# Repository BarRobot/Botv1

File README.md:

# Botv1
BarRobot is a South African design for a Bartending Robot machine.  
It comes with a really easy to use user interface: Selector Switch to choose Single, Double.  And one big red illuminited "Go" button.  Can't be easier!
WS2812B LEDs surround the spirits bottle, helping to invite friends closer - attracted by RGB Blinkies!

## Electronics:
This is a render of the Version 1 Electronics Pack 

## Mascot! 

This is our official Mascot, designed by the talented [LUISDJT](https://www.fiverr.com/luisdjt) - Thanks for the cool Mascot!

## Early prototypes in action

Here's an old version, in use:

(Youtube Link)

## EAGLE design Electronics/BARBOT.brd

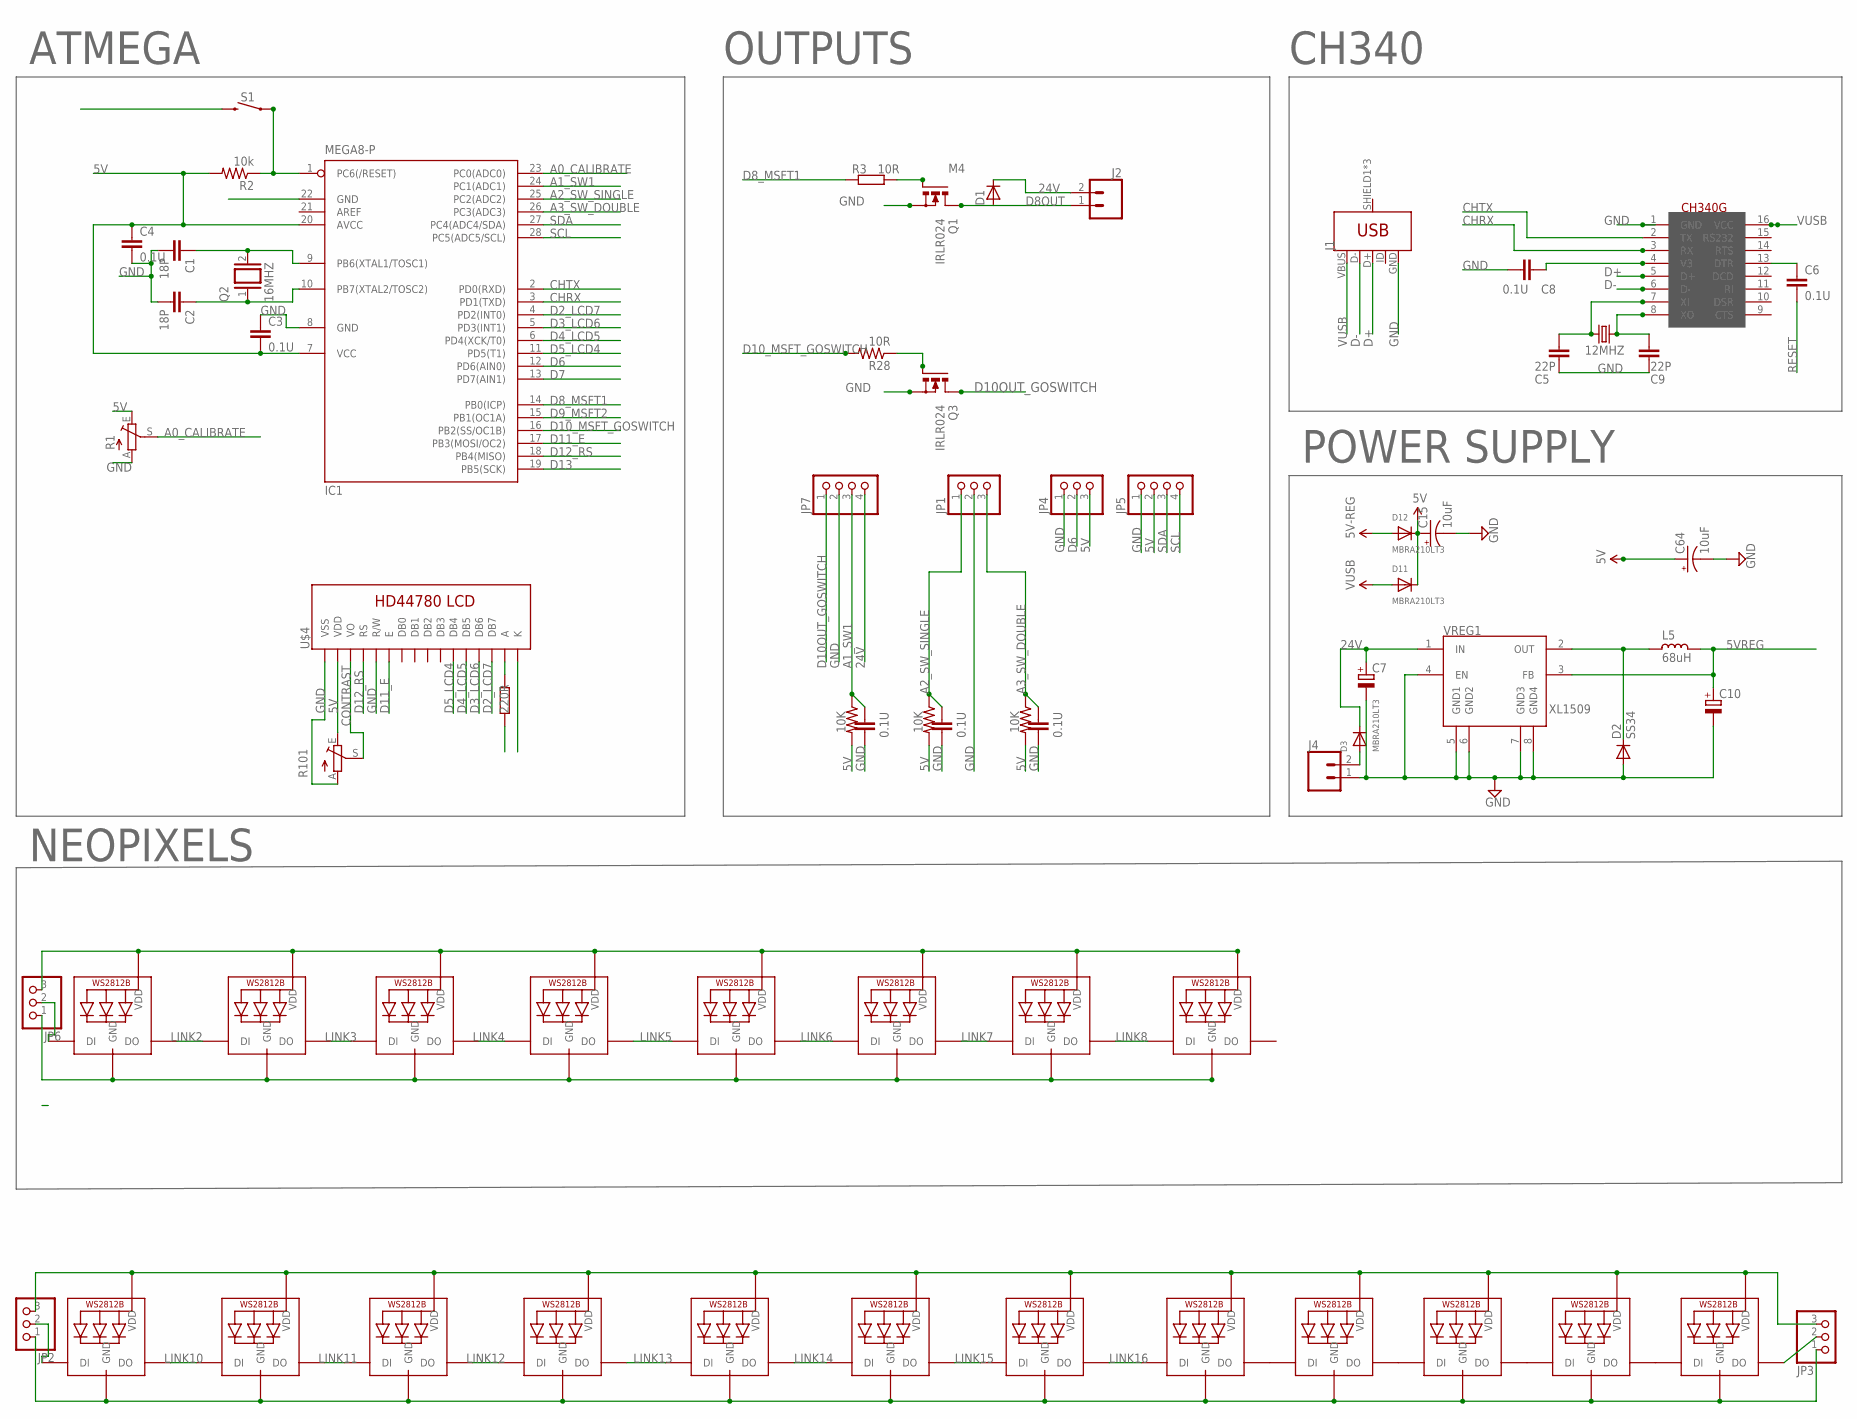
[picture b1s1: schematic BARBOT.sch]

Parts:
12MHZ: 12MHZ; HC49U70
C1, C2: 18P; C1206
C3, C4, C6, C8, C11, C12, C13: 0.1U; C1206
C5, C9: 22P; C1206
C7, C10: CPOL-EUE3.5-10; E3,5-10
C15, C64: 10uF; EIA3216
D1: M4; SOD80
D2: SS34; DO-214AC
D3, D11, D12: MBRA210LT3; SMADIODE
IC1: MEGA8-P; DIL28-3
J1: USB_MICRO-BREDUCED_PASTE; USB-B-MICRO-SMD_RED_PASTE
J2, J4: CONN_023.5MM; SCREWTERMINAL-3.5MM-2
JP1, JP2, JP3, JP4, JP6: PINHD-1X3; 1X03
JP5, JP7: PINHD-1X4; 1X04
L5: 68uH; CD75
LED1, LED2, LED3, LED4, LED5, LED6, LED7, LED8, LED9, LED10, LED11, LED12, LED13, LED14, LED15, LED16, LED17, LED18, LED19, LED20: WS2812B5050; WS2812B
Q1, Q3: IRLR024; D-PAK_TO252AA
Q2: 16MHZ; QS
R1, R101: TRIM_EU-B25P; B25P
R2: 10k; R1206
R3: 10R; R1206
R4: 220R; R1206
R5, R6, R7: 10K; R1206@1
R28: 10R; R1206@1
S1: MOMENTARY-SWITCH-SPST-PTH-RIGHT-ANGLE-KIT; TACTILE_SWITCH_PTH_RIGHT_ANGLE_KIT
U$2: CH340G; SOIC16
U$4: LCD-HD447804-HOLES16X2-4-HOLES; LCD-16X2-4HOLES
VREG1: XL1509; SO08

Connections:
5V: C3.2, C4.1, C15.A (+), C64.A (+), D11.C, D12.C, IC1.7 (VCC), IC1.20 (AVCC), JP4.3, JP5.2, JP6.3, LED1.1-VDD (VDD), LED2.1-VDD (VDD), LED3.1-VDD (VDD), LED4.1-VDD (VDD), LED5.1-VDD (VDD), LED6.1-VDD (VDD), LED7.1-VDD (VDD), LED8.1-VDD (VDD), R1.E, R2.2, R4.1, R5.2, R6.2, R7.2, R101.E, U$4.2 (VDD)
5V1: JP2.3, JP3.3, LED9.1-VDD (VDD), LED10.1-VDD (VDD), LED11.1-VDD (VDD), LED12.1-VDD (VDD), LED13.1-VDD (VDD), LED14.1-VDD (VDD), LED15.1-VDD (VDD), LED16.1-VDD (VDD), LED17.1-VDD (VDD), LED18.1-VDD (VDD), LED19.1-VDD (VDD), LED20.1-VDD (VDD)
5VREG: C10.+, D12.A, L5.1, VREG1.3 (FB)
24V: C7.+, D1.1 (C), D3.C, J2.2, JP7.4, VREG1.1 (IN)
A0_CALIBRATE: IC1.23 (PC0(ADC0)), R1.S
A1_SW1: C11.1, IC1.24 (PC1(ADC1)), JP7.3, R5.1
A2_SW_SINGLE: C12.1, IC1.25 (PC2(ADC2)), JP1.1, R6.1
A3_SW_DOUBLE: C13.1, IC1.26 (PC3(ADC3)), JP1.3, R7.1
CHRX: IC1.3 (PD1(TXD)), U$2.3 (RX)
CHTX: IC1.2 (PD0(RXD)), U$2.2 (TX)
CONTRAST: R101.S, U$4.3 (VO)
D2_LCD7: IC1.4 (PD2(INT0)), U$4.14 (DB7)
D3_LCD6: IC1.5 (PD3(INT1)), U$4.13 (DB6)
D4_LCD5: IC1.6 (PD4(XCK/T0)), U$4.12 (DB5)
D5_LCD4: IC1.11 (PD5(T1)), U$4.11 (DB4)
D6: IC1.12 (PD6(AIN0)), JP4.2
D7: IC1.13 (PD7(AIN1))
D8OUT: D1.2 (A), J2.1, Q1.4 (D)
D8_MSFT1: IC1.14 (PB0(ICP)), R3.1
D9_MSFT2: IC1.15 (PB1(OC1A))
D10OUT_GOSWITCH: JP7.1, Q3.4 (D)
D10_MSFT_GOSWITCH: IC1.16 (PB2(SS/OC1B)), R28.2
D11_E: IC1.17 (PB3(MOSI/OC2)), U$4.6 (E)
D12_RS: IC1.18 (PB4(MISO)), U$4.4 (RS)
D13: IC1.19 (PB5(SCK))
D+: J1.D+, U$2.5 (D+)
D-: J1.D-, U$2.6 (D-)
GND: C1.2, C2.2, C3.1, C4.2, C5.2, C7.-, C8.2, C9.2, C10.-, C11.2, C12.2, C13.2, C15.C (-), C64.C (-), D2.2 (A), IC1.8 (GND), IC1.22 (GND), J1.GND, J4.1, JP1.2, JP4.1, JP5.1, JP6.1, JP7.2, LED1.3-GND (GND), LED2.3-GND (GND), LED3.3-GND (GND), LED4.3-GND (GND), LED5.3-GND (GND), LED6.3-GND (GND), LED7.3-GND (GND), LED8.3-GND (GND), Q1.3 (S), Q3.3 (S), R1.A, R101.A, S1.2, U$2.1 (GND), U$4.1 (VSS), U$4.5 (R/W), U$4.16 (K), VREG1.4 (EN), VREG1.5 (GND1), VREG1.6 (GND2), VREG1.7 (GND3), VREG1.8 (GND4)
GND1: JP2.1, JP3.1, LED9.3-GND (GND), LED10.3-GND (GND), LED11.3-GND (GND), LED12.3-GND (GND), LED13.3-GND (GND), LED14.3-GND (GND), LED15.3-GND (GND), LED16.3-GND (GND), LED17.3-GND (GND), LED18.3-GND (GND), LED19.3-GND (GND), LED20.3-GND (GND)
LINK1: JP6.2, LED1.4-DIN (DI)
LINK2: LED1.2-DOUT (DO), LED2.4-DIN (DI)
LINK3: LED2.2-DOUT (DO), LED3.4-DIN (DI)
LINK4: LED3.2-DOUT (DO), LED4.4-DIN (DI)
LINK5: LED4.2-DOUT (DO), LED5.4-DIN (DI)
LINK6: LED5.2-DOUT (DO), LED6.4-DIN (DI)
LINK7: LED6.2-DOUT (DO), LED7.4-DIN (DI)
LINK8: LED7.2-DOUT (DO), LED8.4-DIN (DI)
LINK9: JP2.2, LED9.4-DIN (DI)
LINK10: LED9.2-DOUT (DO), LED10.4-DIN (DI)
LINK11: LED10.2-DOUT (DO), LED11.4-DIN (DI)
LINK12: LED11.2-DOUT (DO), LED12.4-DIN (DI)
LINK13: LED12.2-DOUT (DO), LED13.4-DIN (DI)
LINK14: LED13.2-DOUT (DO), LED14.4-DIN (DI)
LINK15: LED14.2-DOUT (DO), LED15.4-DIN (DI)
LINK16: LED15.2-DOUT (DO), LED16.4-DIN (DI)
unnamed: Q1.1 (G), R3.2
unnamed: C6.1, U$2.13 (DTR)
unnamed: C1.1, IC1.9 (PB6(XTAL1/TOSC1)), Q2.2
unnamed: D3.A, J4.2
unnamed: C2.1, IC1.10 (PB7(XTAL2/TOSC2)), Q2.1
unnamed: JP3.2, LED20.2-DOUT (DO)
unnamed: LED16.2-DOUT (DO), LED17.4-DIN (DI)
unnamed: LED17.2-DOUT (DO), LED18.4-DIN (DI)
unnamed: 12MHZ.1, C5.1, U$2.7 (XI)
unnamed: R4.2, U$4.15 (A)
unnamed: 12MHZ.2, C9.1, U$2.8 (XO)
unnamed: C8.1, U$2.4 (V3)
unnamed: LED18.2-DOUT (DO), LED19.4-DIN (DI)
unnamed: LED19.2-DOUT (DO), LED20.4-DIN (DI)
unnamed: Q3.1 (G), R28.1
unnamed: D2.1 (C), L5.2, VREG1.2 (OUT)
RESET: C6.2, IC1.1 (PC6(/RESET)), R2.1, S1.1
SCL: IC1.28 (PC5(ADC5/SCL)), JP5.4
SDA: IC1.27 (PC4(ADC4/SDA)), JP5.3
VUSB: D11.A, J1.VBUS, U$2.16 (VCC)

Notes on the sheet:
POWER SUPPLY
OUTPUTS
ATMEGA
CH340
NEOPIXELS

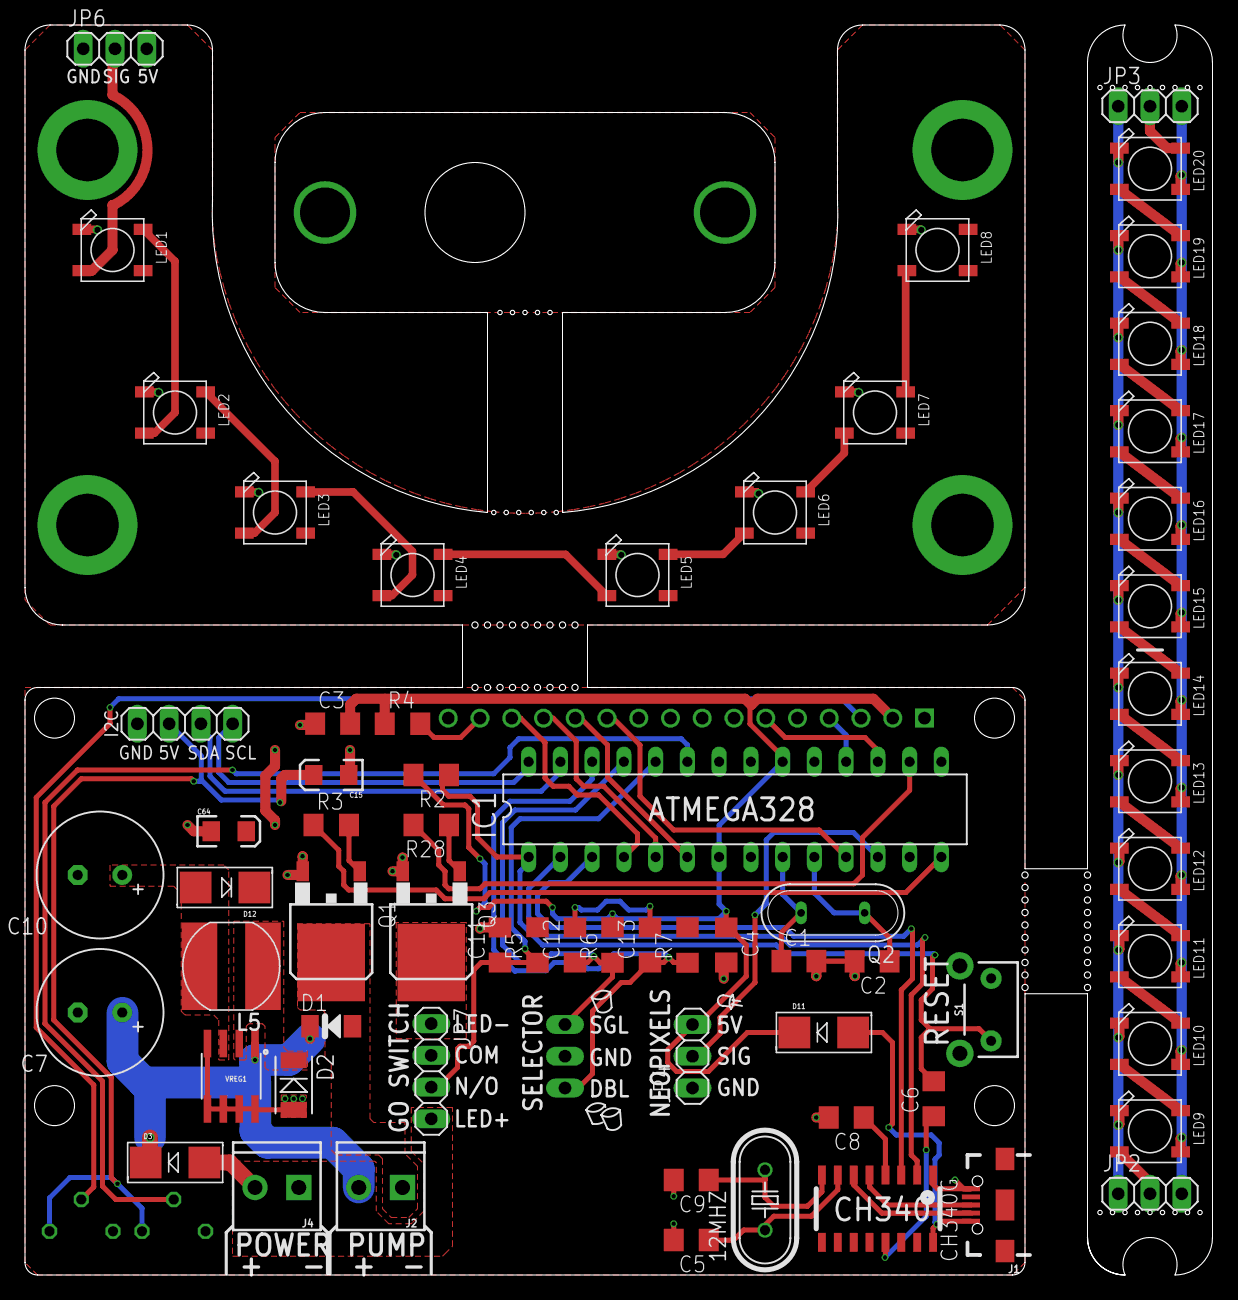
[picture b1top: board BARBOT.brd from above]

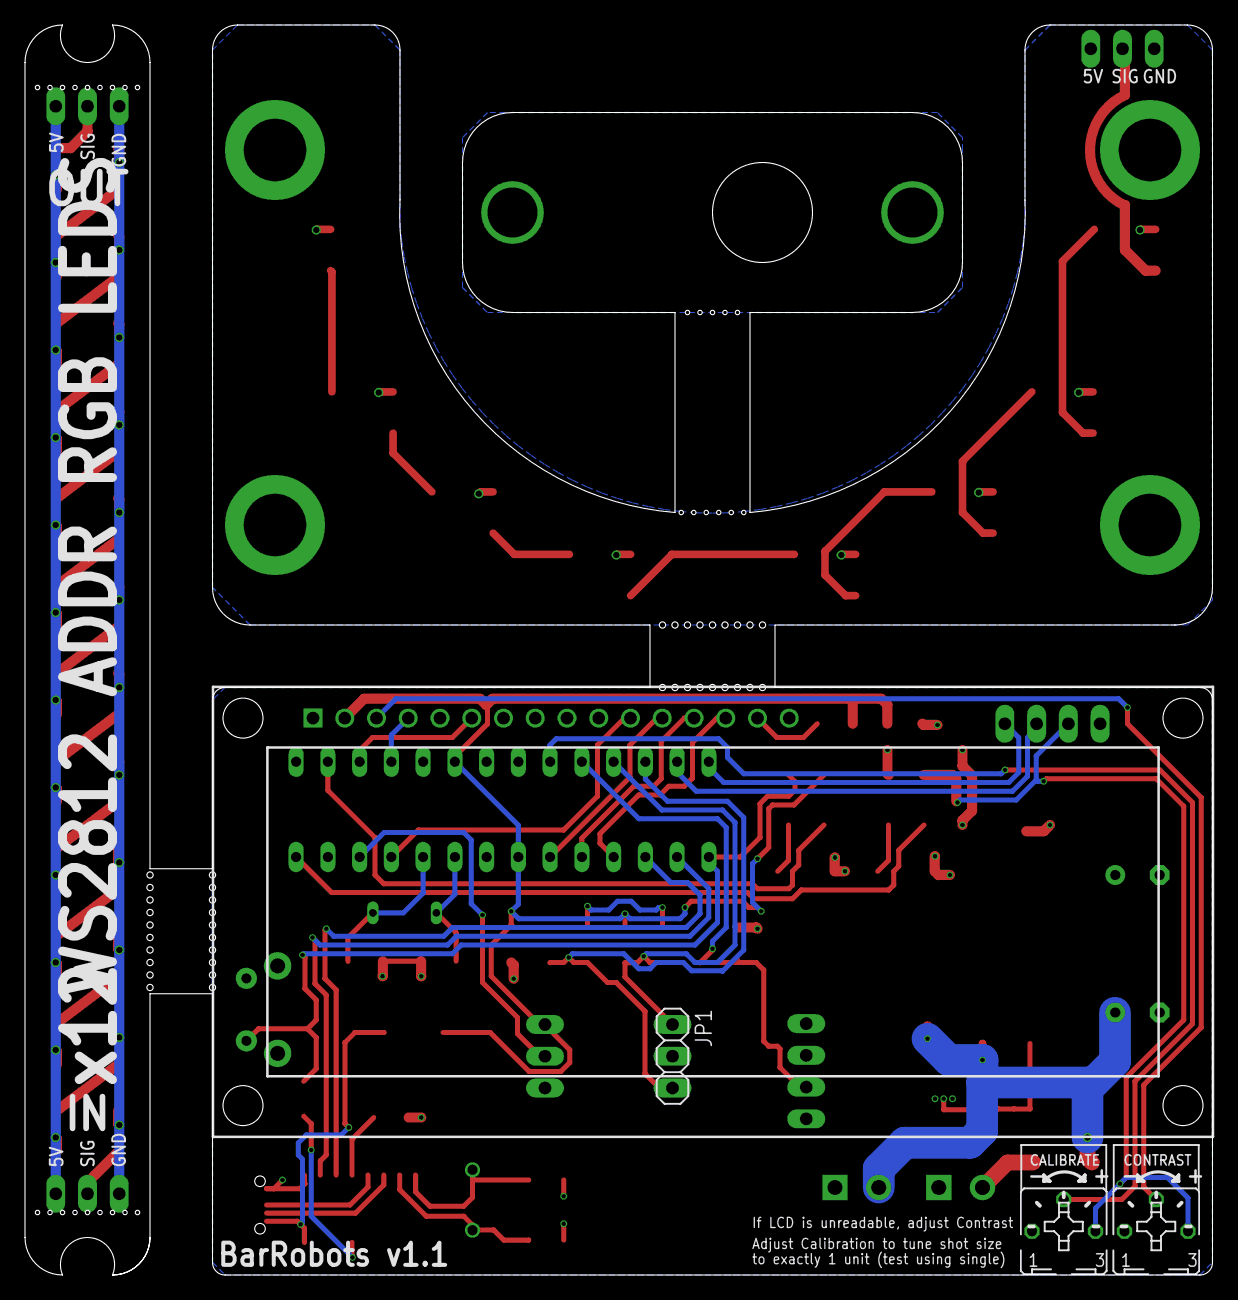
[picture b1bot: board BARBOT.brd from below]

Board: 2 copper layers, 95.0 x 100.0 mm, 69 parts (4 on the bottom side), 62 nets.

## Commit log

2018-03-07 render
2018-03-07 update render
2021-06-08 debadge

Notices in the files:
parts and their libraries:
rc-master-smd: Copyright (C) 2007, Bob Starr
SparkFun-Switches: Licensing: Creative Commons ShareAlike 4.0 International - https://creativecommons.org/licenses/by-sa/4.0
